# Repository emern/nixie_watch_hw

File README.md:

# nixie_watch_hw
Hardware for an IN-16 nixie tube based wristwatch/pocketwatch designed in KiCAD 5.1.3. This project contains PCB for both the watch main-board and Nixie tube holder designed to be mounted perpendicularly to allow the tubes to be visible from above. Watch main-board contains both STM8L based MCU alongside 9v-186v flyback boost converter to supply the large running voltages required by the nixie tubes. More information on the IN-16 nixie tube can be found [here](http://www.tube-tester.com/sites/nixie/data/in16.htm).

## PCBs

There are two induvidual PCBs needed to construct this wristwatch.

* Watch main-board (MCU, power supply, nixie GPIO driver, status LED, input switches)
* Nixie tube holder (Nixie tube socket x2)

## Features

Some features of this watch include:

* 9v battery based power supply
* 9v-186v nixie tube power supply based on flyback boost topology
* Wake button, slider switch to select between various sleep modes
* Status (mins/hours mode) LED indicator
* 2 nixie tube display
* 32mm radius
* [Firmware avaliable](https://github.com/emern/nixie_watch_fw)

## License

This project is licensed under the GPL-3.0 License.

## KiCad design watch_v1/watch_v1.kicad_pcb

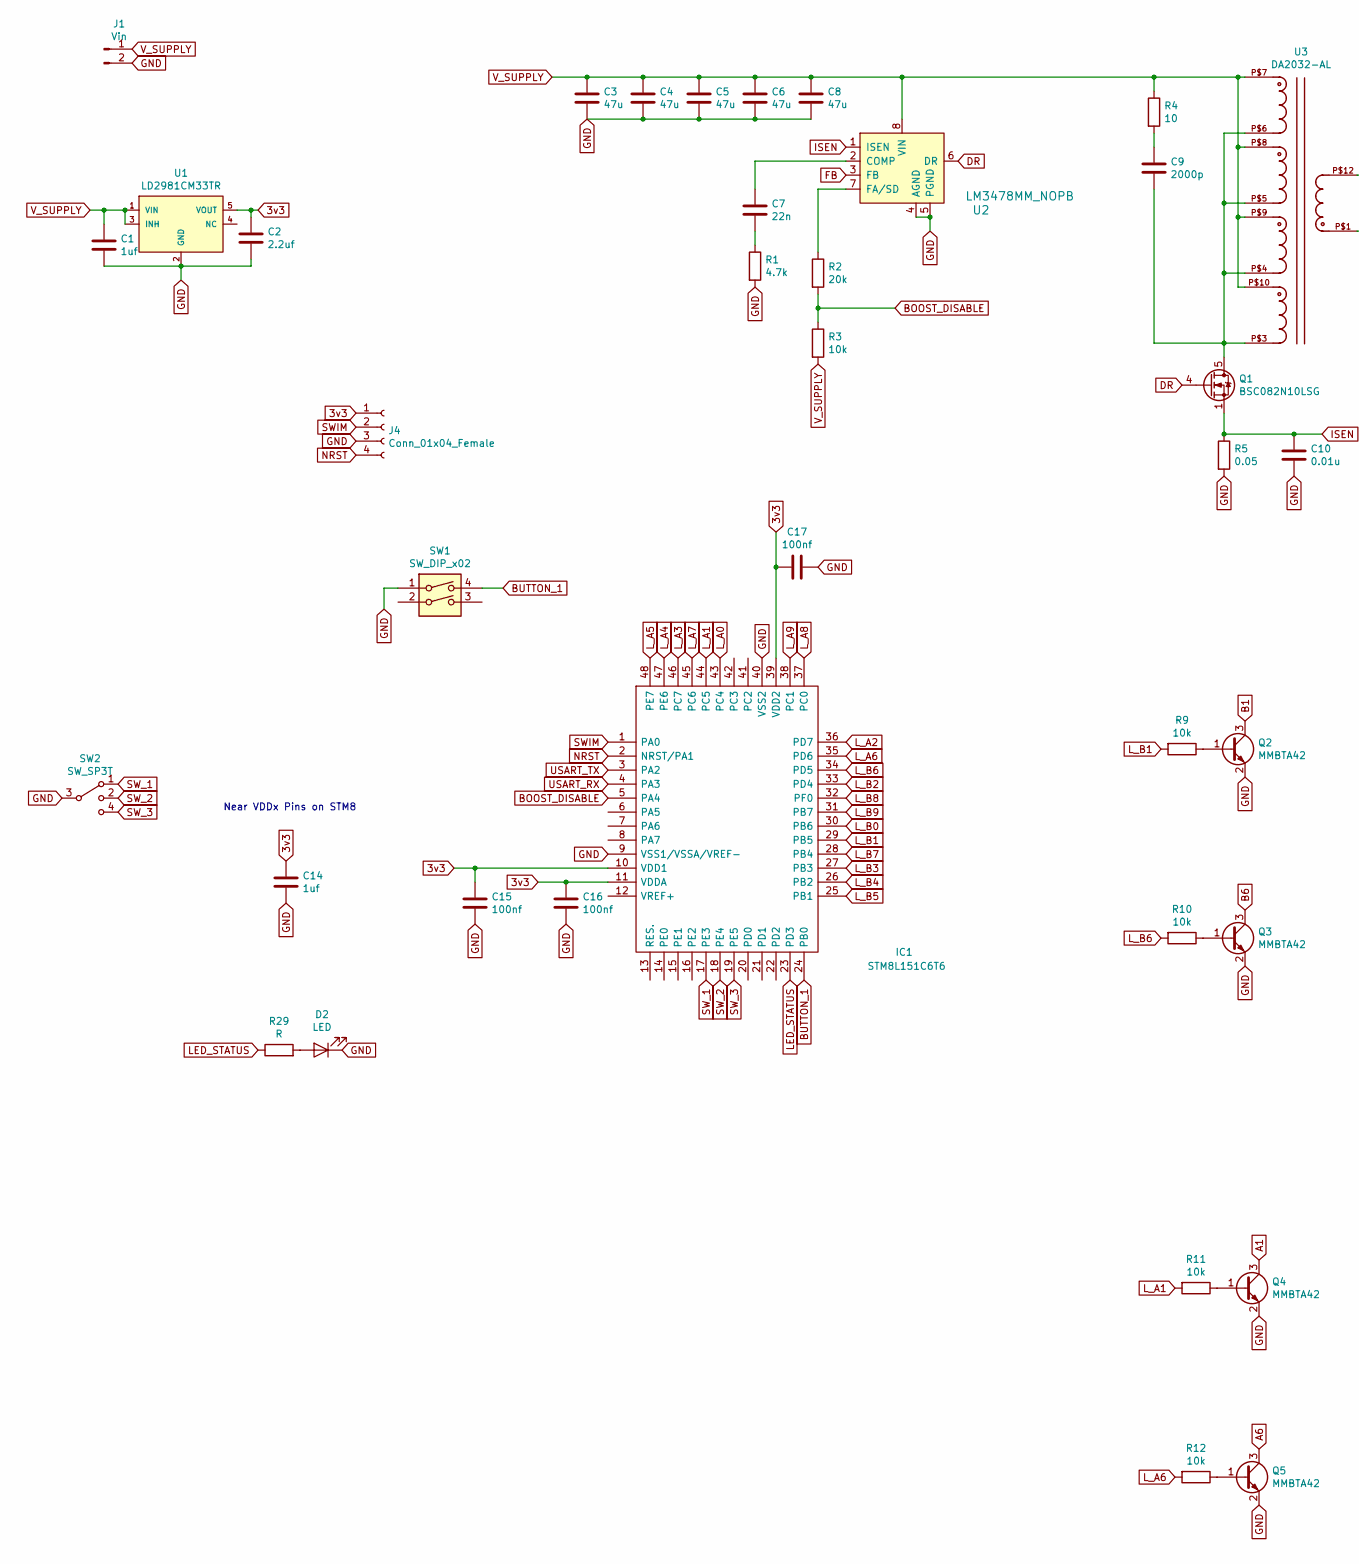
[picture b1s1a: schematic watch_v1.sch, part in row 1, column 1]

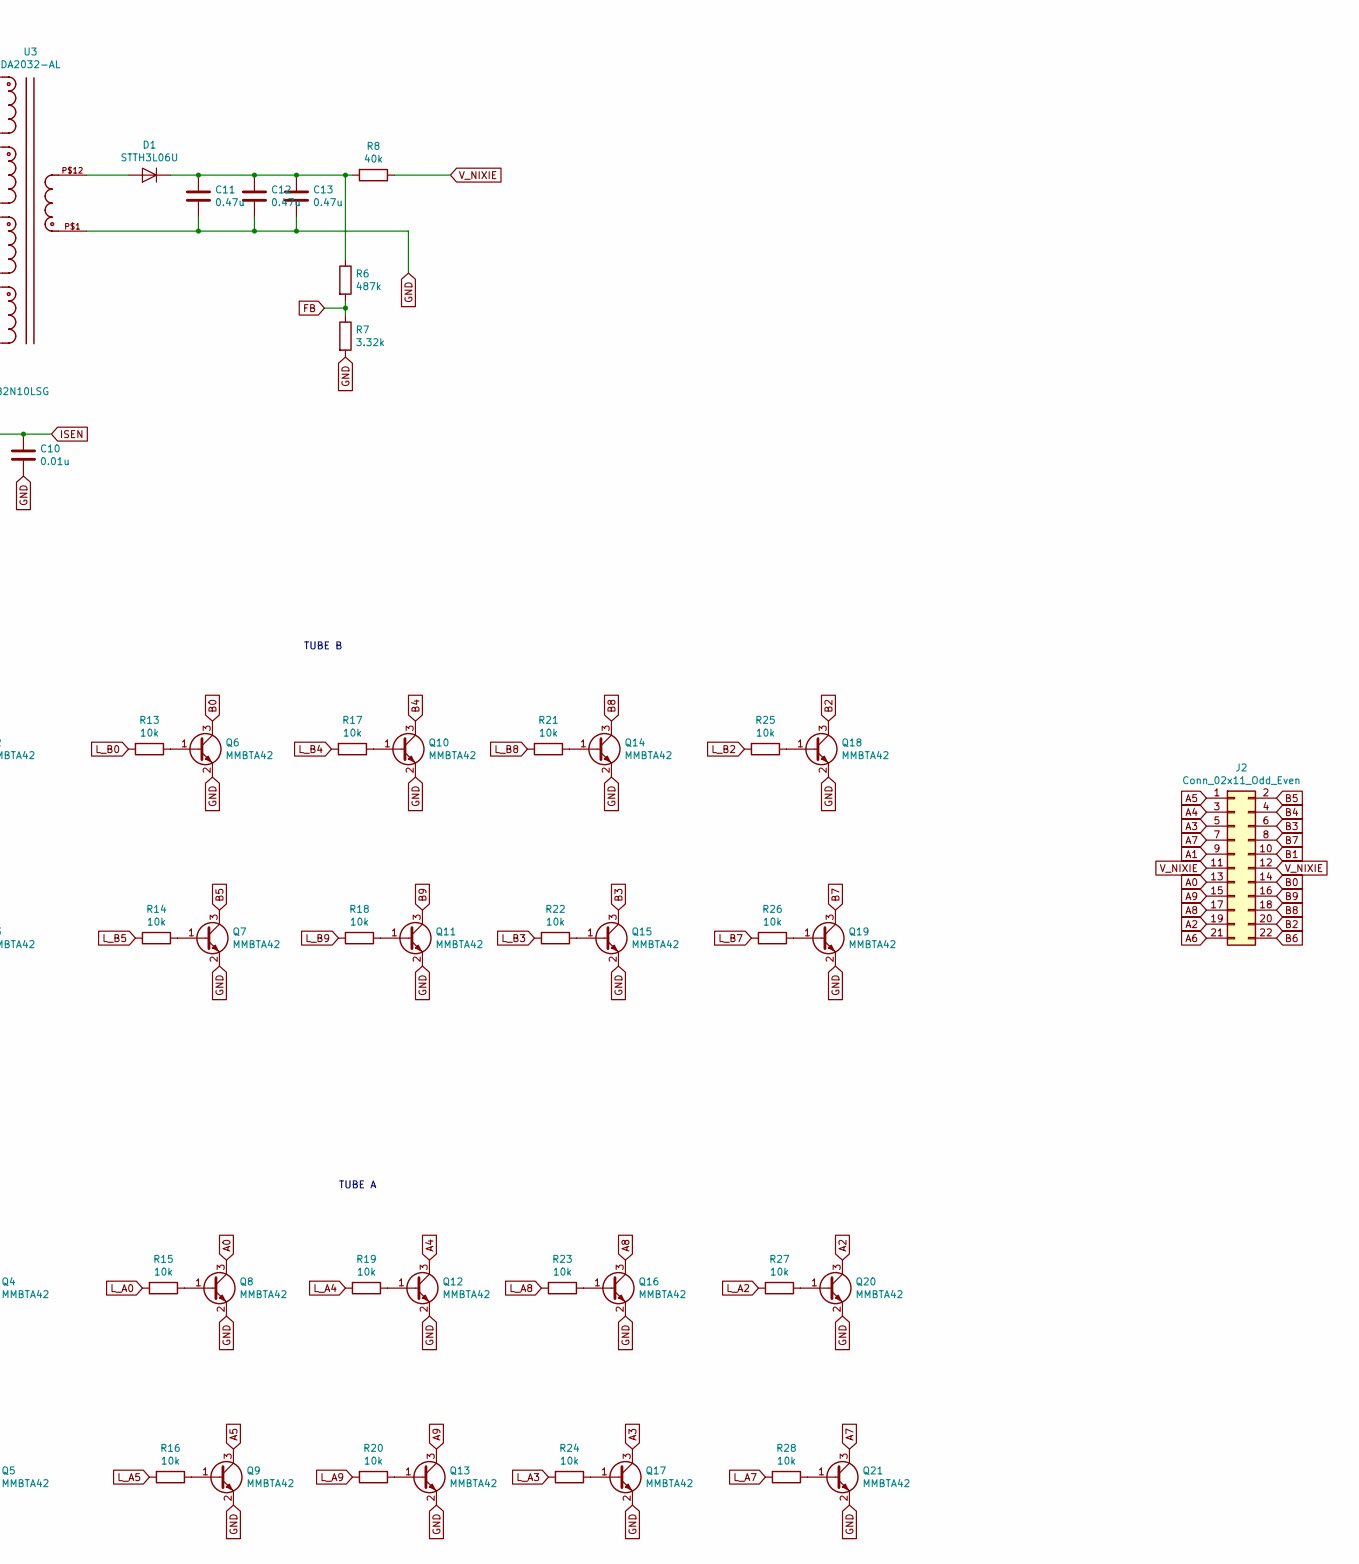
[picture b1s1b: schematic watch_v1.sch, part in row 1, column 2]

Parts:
C1, C14: 1uf; C_1206_3216Metric
C2: 2.2uf; C_0805_2012Metric
C3, C4, C5, C6, C8: 47u; C_0805_2012Metric
C7: 22n; C_0402_1005Metric
C9: 2000p; C_0603_1608Metric
C10: 0.01u; C_0603_1608Metric
C11, C12, C13: 0.47u; C_1210_3225Metric
C15, C16, C17: 100nf; C_0805_2012Metric
D1: STTH3L06U; D_SMB
D2: LED; LED_0402_1005Metric
IC1: STM8L151C6T6; LQFP-48_7x7mm_P0.5mm; Manufacturer_Part_Number STM8L151C6T6; Mouser Part Number 511-STM8L151C6T6
J1: Vin; PinSocket_1x02_P2.54mm_Vertical
J2: Conn_02x11_Odd_Even; PinHeader_Nixie_1_37mm
J4: Conn_01x04_Female; PinHeader_1x04_P2.54mm_Vertical
Q1: BSC082N10LSG; TDSON-8-1
Q2, Q3, Q4, Q5, Q6, Q7, Q8, Q9, Q10, Q11, Q12, Q13, Q14, Q15, Q16, Q17, Q18, Q19, Q20, Q21: MMBTA42; SOT-23
R1: 4.7k; R_0805_2012Metric
R2: 20k; R_0603_1608Metric
R3: 10k; R_0603_1608Metric
R4: 10; R_0805_2012Metric
R5: 0.05; R_0402_1005Metric
R6: 487k; R_0805_2012Metric
R7: 3.32k; R_0603_1608Metric
R8: 40k; R_1206_3216Metric
R9, R10, R11, R12, R13, R14, R15, R16, R17, R18, R19, R20, R21, R22, R23, R24, R25, R26, R27, R28: 10k; R_0402_1005Metric
R29: R; R_1206_3216Metric
SW1: SW_DIP_x02; CK-PTS526SK15SMTR2LFS-0-0-MFG
SW2: SW_SP3T; SW_PCM13SMTR
U1: LD2981CM33TR; SOT-23-5
U2: LM3478MM_NOPB; SOIC-8_W3.9mm; MPN LM3478MM/NOPB; Digi-Key_PN LM3478MM/NOPBCT-ND
U3: DA2032-AL

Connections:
3v3: C2.1, C14.1, C15.1, C16.1, C17.2, IC1.10 (VDD1), IC1.11 (VDDA), IC1.39 (VDD2), J4.1, U1.5 (VOUT)
A0: J2.13, Q8.3 (C)
A1: J2.9, Q4.3 (C)
A2: J2.19, Q20.3 (C)
A3: J2.5, Q17.3 (C)
A4: J2.3, Q12.3 (C)
A5: J2.1, Q9.3 (C)
A6: J2.21, Q5.3 (C)
A7: J2.7, Q21.3 (C)
A8: J2.17, Q16.3 (C)
A9: J2.15, Q13.3 (C)
B0: J2.14, Q6.3 (C)
B1: J2.10, Q2.3 (C)
B2: J2.20, Q18.3 (C)
B3: J2.6, Q15.3 (C)
B4: J2.4, Q10.3 (C)
B5: J2.2, Q7.3 (C)
B6: J2.22, Q3.3 (C)
B7: J2.8, Q19.3 (C)
B8: J2.18, Q14.3 (C)
B9: J2.16, Q11.3 (C)
BOOST_DISABLE: IC1.5 (PA4), R2.2, R3.1
BUTTON_1: IC1.24 (PB0), SW1.4
DR: Q1.4 (G), U2.6 (DR)
FB: R6.2, R7.1, U2.3 (FB)
GND: C1.2, C2.2, C3.2, C4.2, C5.2, C6.2, C8.2, C10.2, C11.2, C12.2, C13.2, C14.2, C15.2, C16.2, C17.1, D2.1 (K), IC1.9 (VSS1/VSSA/VREF-), IC1.40 (VSS2), J1.2, J4.3, Q2.2 (E), Q3.2 (E), Q4.2 (E), Q5.2 (E), Q6.2 (E), Q7.2 (E), Q8.2 (E), Q9.2 (E), Q10.2 (E), Q11.2 (E), Q12.2 (E), Q13.2 (E), Q14.2 (E), Q15.2 (E), Q16.2 (E), Q17.2 (E), Q18.2 (E), Q19.2 (E), Q20.2 (E), Q21.2 (E), R1.2, R5.2, R7.2, SW1.1, SW2.3, U1.2 (GND), U2.4 (AGND), U2.5 (PGND), U3.P$1
ISEN: C10.1, Q1.1 (S), Q1.2 (S), Q1.3 (S), R5.1, U2.1 (ISEN)
LED_STATUS: IC1.23 (PD3), R29.1
L_A0: IC1.43 (PC4), R15.2
L_A1: IC1.44 (PC5), R11.2
L_A2: IC1.36 (PD7), R27.2
L_A3: IC1.46 (PC7), R24.2
L_A4: IC1.47 (PE6), R19.2
L_A5: IC1.48 (PE7), R16.2
L_A6: IC1.35 (PD6), R12.2
L_A7: IC1.45 (PC6), R28.2
L_A8: IC1.37 (PC0), R23.2
L_A9: IC1.38 (PC1), R20.2
L_B0: IC1.30 (PB6), R13.2
L_B1: IC1.29 (PB5), R9.2
L_B2: IC1.33 (PD4), R25.2
L_B3: IC1.27 (PB3), R22.2
L_B4: IC1.26 (PB2), R17.2
L_B5: IC1.25 (PB1), R14.2
L_B6: IC1.34 (PD5), R10.2
L_B7: IC1.28 (PB4), R26.2
L_B8: IC1.32 (PF0), R21.2
L_B9: IC1.31 (PB7), R18.2
NRST: IC1.2 (NRST/PA1), J4.4
unnamed: C7.1, U2.2 (COMP)
unnamed: C7.2, R1.1
unnamed: C9.1, R4.2
unnamed: C9.2, Q1.5 (D), U3.P$3, U3.P$4, U3.P$5, U3.P$6
unnamed: C11.1, C12.1, C13.1, D1.1 (K), R6.1, R8.2
unnamed: D1.2 (A), U3.P$12
unnamed: D2.2 (A), R29.2
unnamed: Q2.1 (B), R9.1
unnamed: Q3.1 (B), R10.1
unnamed: Q4.1 (B), R11.1
unnamed: Q5.1 (B), R12.1
unnamed: Q6.1 (B), R13.1
unnamed: Q7.1 (B), R14.1
unnamed: Q8.1 (B), R15.1
unnamed: Q9.1 (B), R16.1
unnamed: Q10.1 (B), R17.1
unnamed: Q11.1 (B), R18.1
unnamed: Q12.1 (B), R19.1
unnamed: Q13.1 (B), R20.1
unnamed: Q14.1 (B), R21.1
unnamed: Q15.1 (B), R22.1
unnamed: Q16.1 (B), R23.1
unnamed: Q17.1 (B), R24.1
unnamed: Q18.1 (B), R25.1
unnamed: Q19.1 (B), R26.1
unnamed: Q20.1 (B), R27.1
unnamed: Q21.1 (B), R28.1
unnamed: R2.1, U2.7 (FA/SD)
SWIM: IC1.1 (PA0), J4.2
SW_1: IC1.17 (PE3), SW2.1
SW_2: IC1.18 (PE4), SW2.2
SW_3: IC1.19 (PE5), SW2.4
USART_RX: IC1.4 (PA3)
USART_TX: IC1.3 (PA2)
V_NIXIE: J2.11, J2.12, R8.1
V_SUPPLY: C1.1, C3.1, C4.1, C5.1, C6.1, C8.1, J1.1, R3.2, R4.1, U1.1 (VIN), U1.3 (INH), U2.8 (VIN), U3.P$7, U3.P$8, U3.P$9, U3.P$10

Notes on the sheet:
Near VDDx Pins on STM8
TUBE B
TUBE A

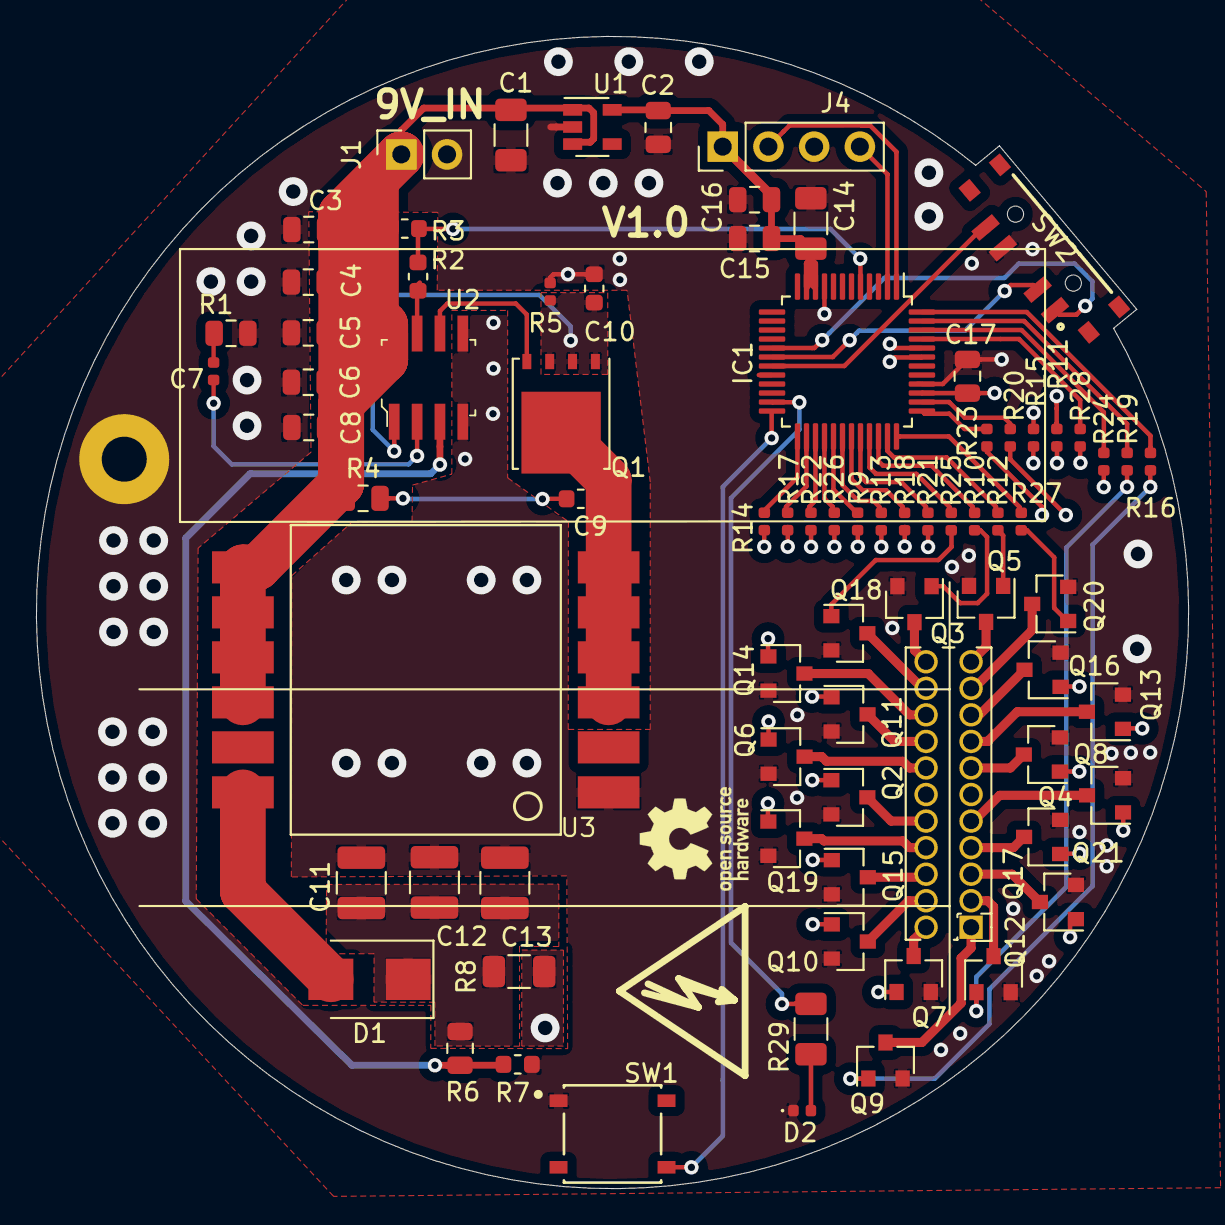
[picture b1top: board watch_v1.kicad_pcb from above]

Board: 4 copper layers, 64.0 x 64.0 mm, 78 parts (0 on the bottom side), 83 nets.

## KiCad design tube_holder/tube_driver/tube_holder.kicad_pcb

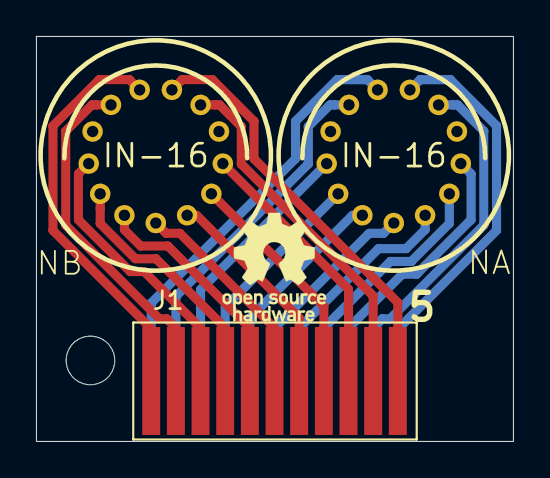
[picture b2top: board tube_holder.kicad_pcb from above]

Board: 2 copper layers, 26.5 x 22.5 mm, 4 parts (1 on the bottom side), 22 nets.

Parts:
J1, J2: Conn_01x11_Female; smd_nixie_header_socket
NA: IN-16; nixies-us-IN-16
NB: IN-16; nixies-us-IN-16

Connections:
A0: J2.5, NA.0
A1: J2.7, NA.1
A2: J2.2, NA.2
A3: J2.9, NA.3
A4: J2.10, NA.4
A5: J2.11, NA.5
A6: J2.1, NA.6
A7: J2.8, NA.7
A8: J2.3, NA.8
A9: J2.4, NA.9
B0: J1.5, NB.0
B1: J1.7, NB.1
B2: J1.2, NB.2
B3: J1.9, NB.3
B4: J1.10, NB.4
B5: J1.11, NB.5
B6: J1.1, NB.6
B7: J1.8, NB.7
B8: J1.3, NB.8
B9: J1.4, NB.9
VA: J2.6, NA.A
VB: J1.6, NB.A

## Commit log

2022-01-03 adding hardware files
2022-01-03 clean up files
2022-01-03 clean up tube holder files
